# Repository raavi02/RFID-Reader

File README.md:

# RFID-Reader
Course project for EDL'23

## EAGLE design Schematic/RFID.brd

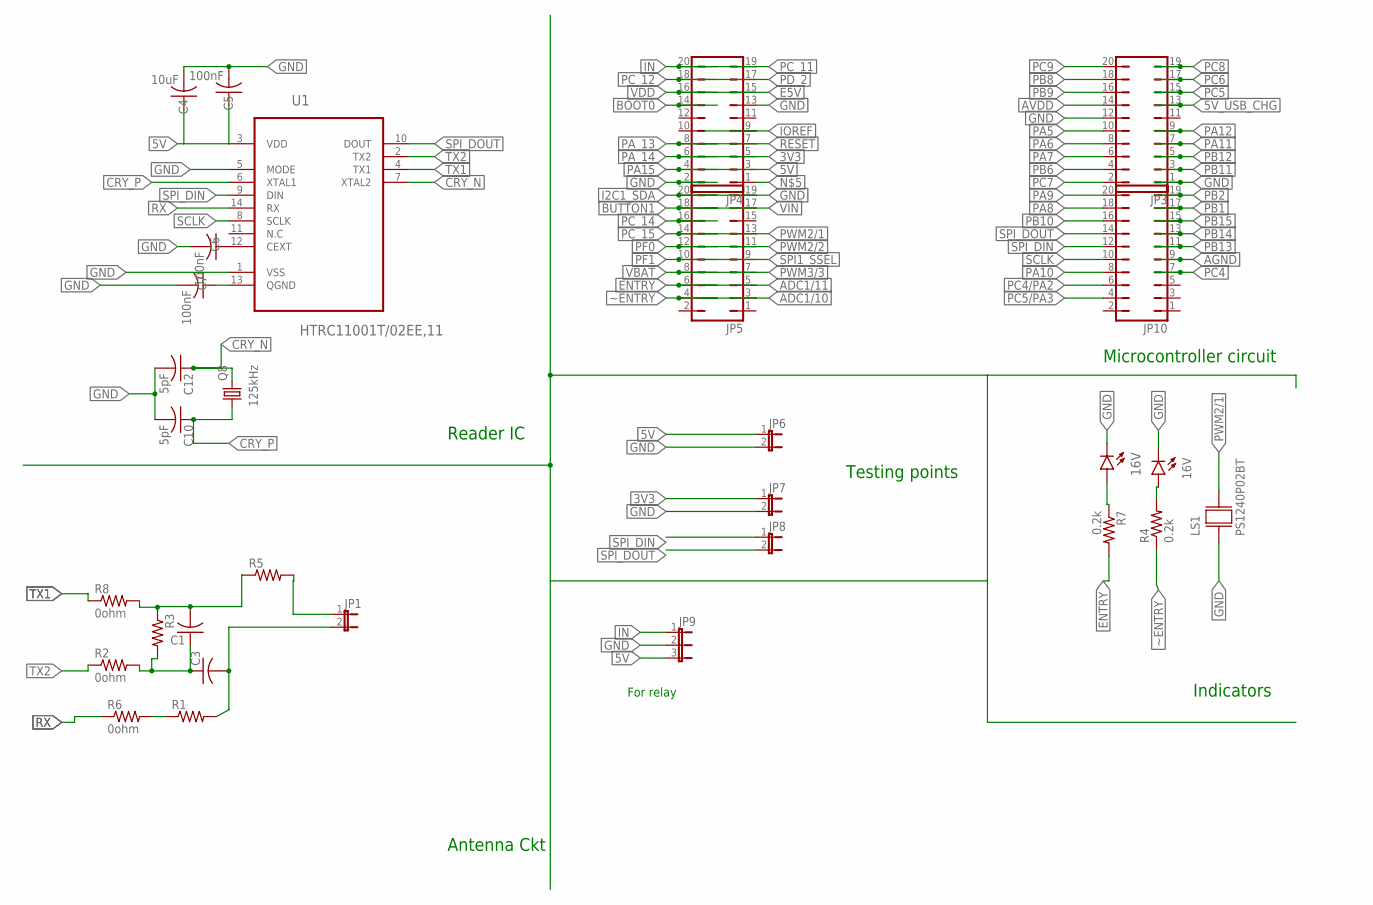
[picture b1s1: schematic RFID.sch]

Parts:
C1, C3: C-USC0805; C0805
C4: 10uF; C0805
C5, C6, C7: 100nF; C0805
C10, C12: 5pF; C025-024X044
GLED: 16V; LED5MM
JP1, JP6, JP7, JP8: JP1E; JP1
JP3, JP4, JP5, JP10: JP10Q
JP9: JP2E; JP2
LS1: PS1240P02BT; XDCR_PS1240P02BT
Q8: 125kHz; HC49/S
R1, R3, R5: R-US_R0603; R0603
R2, R6, R8: 0ohm; R0603
R4, R7: 0.2k; R0603
RLED: 16V; LED5MM
U1: HTRC11001T/02EE,11; SOIC127P600X175-14N

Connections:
3V3: JP4.5, JP7.1
5V: C4.1, C5.1, JP4.3, JP6.1, JP9.3, U1.3 (VDD)
5V_USB_CHG: JP3.13
ADC1/10: JP5.3
ADC1/11: JP5.5
AGND: JP10.9
ANT1: JP1.1, R5.2
ANT2: C3.2, JP1.2, R1.2
ANT3: C1.1, C3.1, R2.2, R3.2
ANT4: C1.2, R3.1, R5.1, R8.2
AVDD: JP3.14
BOOT0: JP4.14
BUTTON1: JP5.18
CRY_N: C12.1, Q8.2, U1.7 (XTAL2)
CRY_P: C10.1, Q8.1, U1.6 (XTAL1)
E5V: JP4.15
ENTRY: JP5.6, R7.2
GND: C4.2, C5.2, C6.2, C7.2, C10.2, C12.2, GLED.K (C), JP3.1, JP3.12, JP4.2, JP4.13, JP5.19, JP6.2, JP7.2, JP9.2, LS1.1, RLED.K (C), U1.1 (VSS), U1.5 (MODE)
I2C1_SDA: JP5.20
IN: JP4.20, JP9.1
IOREF: JP4.9
unnamed: GLED.A, R4.2
unnamed: R7.1, RLED.A
unnamed: R1.1, R6.2
unnamed: C6.1, U1.12 (CEXT)
unnamed: C7.1, U1.13 (QGND)
PA5: JP3.10
PA6: JP3.8
PA7: JP3.6
PA8: JP10.18
PA9: JP10.20
PA10: JP10.8
PA11: JP3.7
PA12: JP3.9
PA15: JP4.4
PA_13: JP4.8
PA_14: JP4.6
PB1: JP10.17
PB2: JP10.19
PB6: JP3.4
PB8: JP3.18
PB9: JP3.16
PB10: JP10.16
PB11: JP3.3
PB12: JP3.5
PB13: JP10.11
PB14: JP10.13
PB15: JP10.15
PC4: JP10.7
PC4/PA2: JP10.6
PC5: JP3.15
PC5/PA3: JP10.4
PC6: JP3.17
PC7: JP3.2
PC8: JP3.19
PC9: JP3.20
PC_11: JP4.19
PC_12: JP4.18
PC_14: JP5.16
PC_15: JP5.14
PD_2: JP4.17
PF0: JP5.12
PF1: JP5.10
PWM2/1: JP5.13, LS1.2
PWM2/2: JP5.11
PWM3/3: JP5.7
RESET: JP4.7
RX: R6.1, U1.14 (RX)
SCLK: JP10.10, U1.8 (SCLK)
SPI1_SSEL: JP5.9
SPI_DIN: JP8.1, JP10.12, U1.9 (DIN)
SPI_DOUT: JP8.2, JP10.14, U1.10 (DOUT)
TX1: R8.1, U1.4 (TX1)
TX2: R2.1, U1.2 (TX2)
VBAT: JP5.8
VDD: JP4.16
VIN: JP5.17
~ENTRY: JP5.4, R4.1

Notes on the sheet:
Reader IC
Antenna Ckt
Microcontroller circuit
Testing points
Indicators
For relay

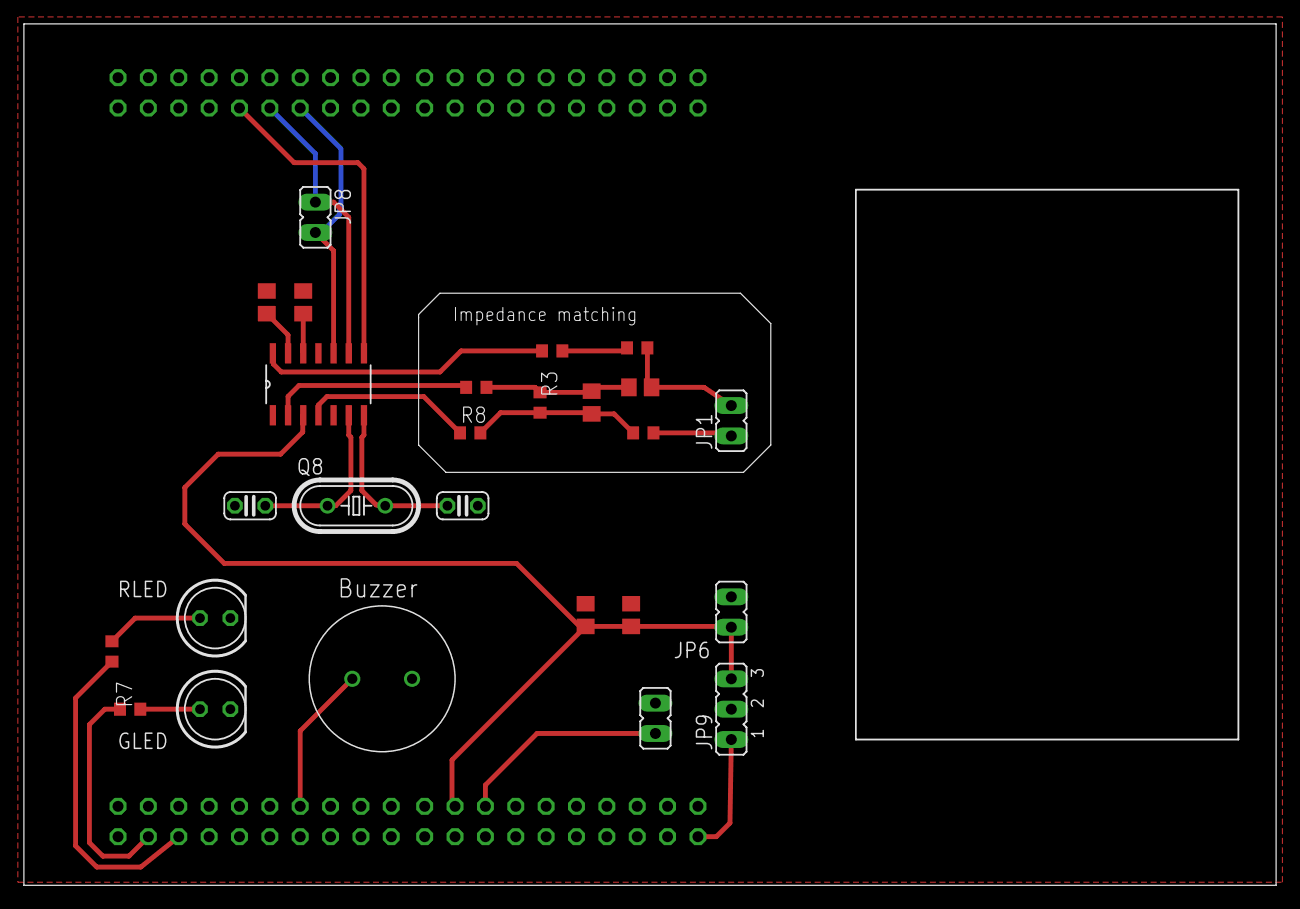
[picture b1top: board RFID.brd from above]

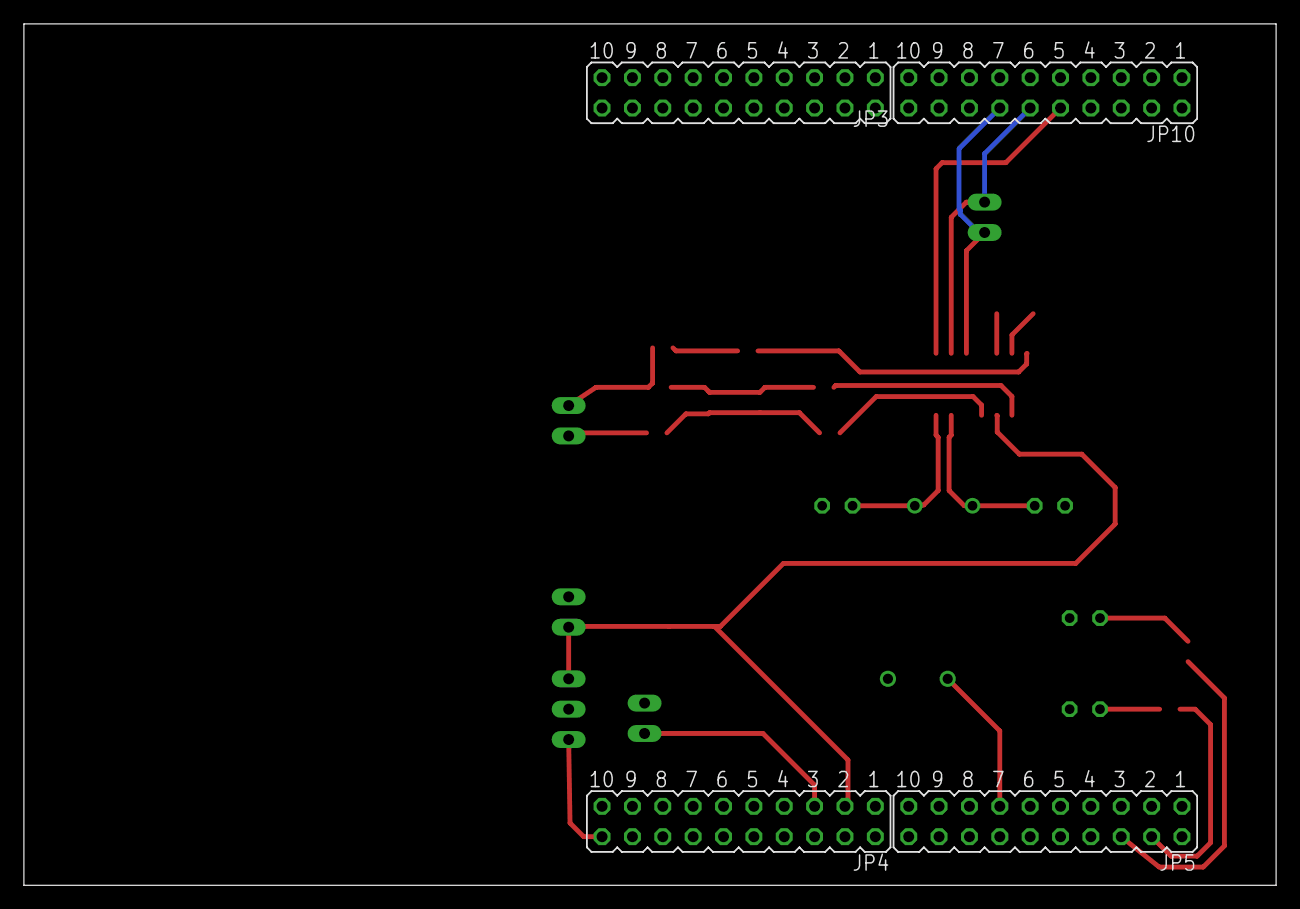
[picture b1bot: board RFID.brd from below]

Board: 2 copper layers, 104.8 x 72.1 mm, 30 parts (4 on the bottom side), 24 nets.

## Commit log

2023-02-07 Schematic -Iter1
2023-02-14 IC Connections, STM32 Pins
2023-02-25 Aesthetics improved
2023-02-25 Schematic without impedance matching
2023-02-26 Buzzer+impedance matching ckt incorporated
2023-02-27 Schematic v1
2023-03-17 Placed board iter1
2023-03-20 Code_v1
2023-03-21 Added antenna to the board
    Need to mirror the jumpers properly
2023-03-25 Final routed board (Hopefully)
2023-03-25 Code v_2
2023-03-25 RFID_newIOC
2023-03-25 RFID_v3
2023-03-27 Testing codes uploaded
2023-03-28 Realterm Working code
